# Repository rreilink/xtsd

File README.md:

XTSD 
====

XTSD is an ISA card that adds an SD-card slot to old PCs using an ISA interface. This project is work in progress.

Repo structure
--------------

| folder | description |
|--------|-------------|
|hardware| Schematic and PCB design in KiCAD |
|hardware-output | Schematic as PDF and Gerber layout files for ordering the PCB |
|GAL | Source and JEDEC binary file for the programmable logic chip U6 (ATF22V10) |

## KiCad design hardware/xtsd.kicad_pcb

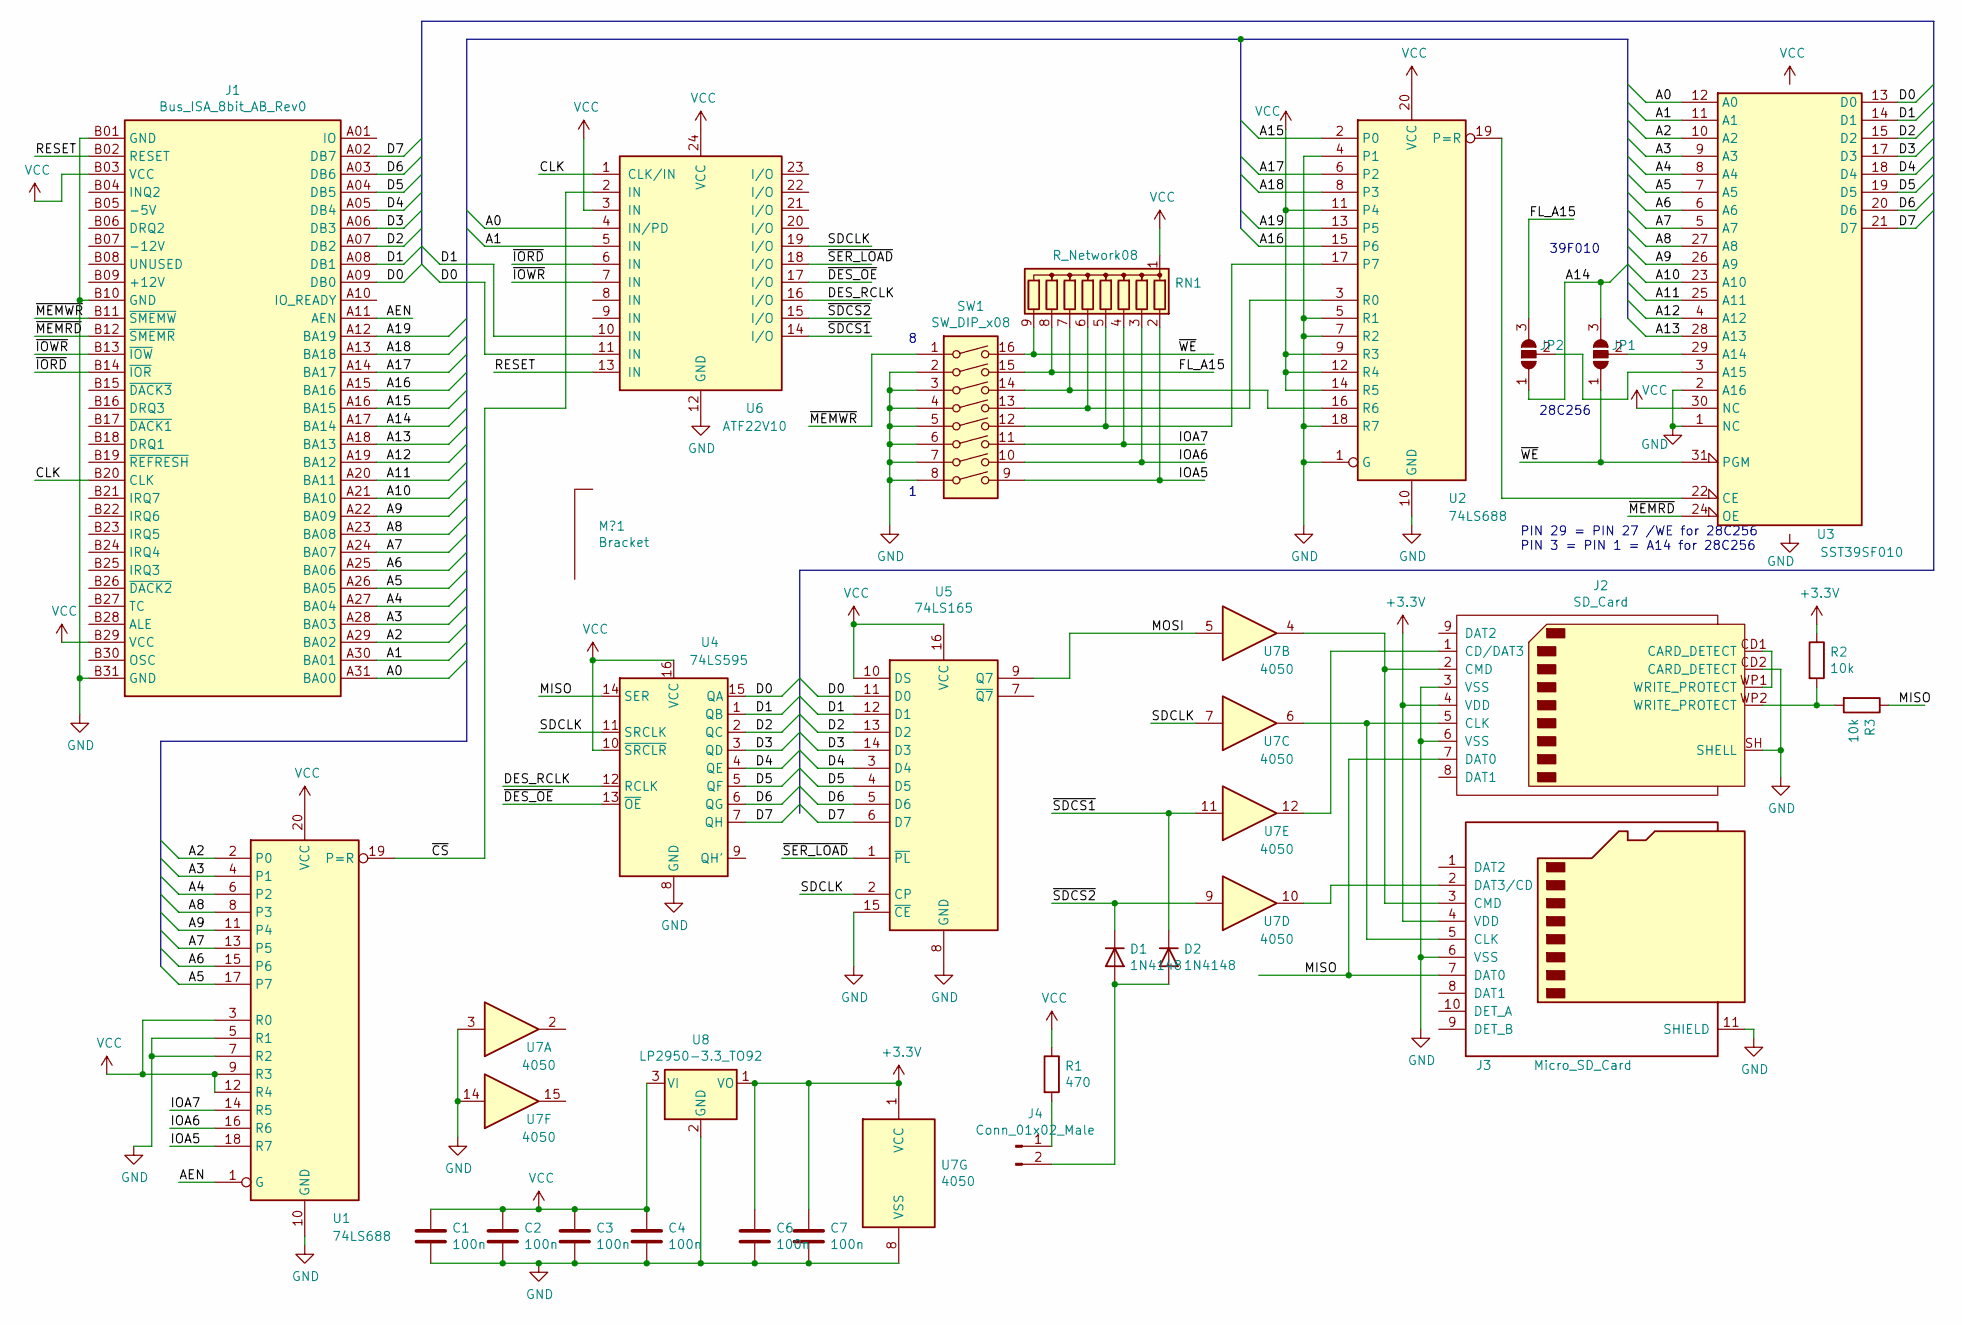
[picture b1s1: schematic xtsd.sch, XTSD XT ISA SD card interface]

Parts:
C1, C2, C3, C4, C6, C7: 100n; C_Disc_D4.3mm_W1.9mm_P5.00mm
D1, D2: 1N4148; D_DO-35_SOD27_P7.62mm_Horizontal
J1: Bus_ISA_8bit_AB_Rev0; ISA_CARD_EDGE_CONNECTOR_8BIT_Rev1
J2: SD_Card; Molex_503500-0991
J3: Micro_SD_Card; microSD_HC_Molex_104031-0811; Farnell 2678573
J4: Conn_01x02_Male; PinHeader_1x02_P2.54mm_Horizontal
JP1, JP2: SolderJumper_3_Open; SolderJumper-3_P2.0mm_Open_TrianglePad1.0x1.5mm_NumberLabels
M?1: Bracket; PC_BRACKET_ISA_KEYSTONE_9202_Rev1
R1: 470; R_Axial_DIN0207_L6.3mm_D2.5mm_P7.62mm_Horizontal
R2, R3: 10k; R_Axial_DIN0207_L6.3mm_D2.5mm_P7.62mm_Horizontal
RN1: R_Network08; R_Array_SIP9
SW1: SW_DIP_x08; SW_DIP_SPSTx08_Slide_9.78x22.5mm_W7.62mm_P2.54mm
U1, U2: 74LS688; DIP-20_W7.62mm_LongPads
U3: SST39SF010; DIP-32_W15.24mm_Socket_LongPads
U4: 74LS595; DIP-16_W7.62mm_LongPads
U5: 74LS165; DIP-16_W7.62mm_LongPads
U6: ATF22V10; DIP-24_W7.62mm_Socket_LongPads
U7: 4050; DIP-16_W7.62mm_LongPads
U8: LP2950-3.3_TO92; TO-92_Inline

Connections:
+3V3: C6.1, C7.1, J2.4 (VDD), J3.4 (VDD), R2.1, U7.1 (VCC), U8.1 (VO)
/A0: J1.A31 (BA00), U3.12 (A0), U6.4 (IN/PD)
/A1: J1.A30 (BA01), U3.11 (A1), U6.5 (IN)
/A2: J1.A29 (BA02), U1.2 (P0), U3.10 (A2)
/A3: J1.A28 (BA03), U1.4 (P1), U3.9 (A3)
/A4: J1.A27 (BA04), U1.6 (P2), U3.8 (A4)
/A5: J1.A26 (BA05), U1.17 (P7), U3.7 (A5)
/A6: J1.A25 (BA06), U1.15 (P6), U3.6 (A6)
/A7: J1.A24 (BA07), U1.13 (P5), U3.5 (A7)
/A8: J1.A23 (BA08), U1.8 (P3), U3.27 (A8)
/A9: J1.A22 (BA09), U1.11 (P4), U3.26 (A9)
/A10: J1.A21 (BA10), U3.23 (A10)
/A11: J1.A20 (BA11), U3.25 (A11)
/A12: J1.A19 (BA12), U3.4 (A12)
/A13: J1.A18 (BA13), U3.28 (A13)
/A14: J1.A17 (BA14), JP1.3 (B), JP2.1 (A)
/A15: J1.A16 (BA15), U2.2 (P0)
/A16: J1.A15 (BA16), U2.15 (P6)
/A17: J1.A14 (BA17), U2.6 (P2)
/A18: J1.A13 (BA18), U2.8 (P3)
/A19: J1.A12 (BA19), U2.13 (P5)
/AEN: J1.A11 (AEN), U1.1 (G)
/CLK: J1.B20 (CLK), U6.1 (CLK/IN)
/D0: J1.A09 (DB0), U3.13 (D0), U4.15 (QA), U5.11 (D0), U6.11 (IN)
/D1: J1.A08 (DB1), U3.14 (D1), U4.1 (QB), U5.12 (D1), U6.10 (IN)
/D2: J1.A07 (DB2), U3.15 (D2), U4.2 (QC), U5.13 (D2)
/D3: J1.A06 (DB3), U3.17 (D3), U4.3 (QD), U5.14 (D3)
/D4: J1.A05 (DB4), U3.18 (D4), U4.4 (QE), U5.3 (D4)
/D5: J1.A04 (DB5), U3.19 (D5), U4.5 (QF), U5.4 (D5)
/D6: J1.A03 (DB6), U3.20 (D6), U4.6 (QG), U5.5 (D6)
/D7: J1.A02 (DB7), U3.21 (D7), U4.7 (QH), U5.6 (D7)
/DES_RCLK: U4.12 (RCLK), U6.16 (I/O)
/FL_A15: JP2.3 (B), RN1.8 (R7), SW1.15
/IOA5: RN1.2 (R1), SW1.9, U1.18 (R7)
/IOA6: RN1.3 (R2), SW1.10, U1.16 (R6)
/IOA7: RN1.4 (R3), SW1.11, U1.14 (R5)
/MISO: J2.7 (DAT0), J3.7 (DAT0), R3.1, U4.14 (SER)
/MOSI: U5.9 (Q7), U7.5
/RESET: J1.B02 (RESET), U6.13 (IN)
/SDCLK: U4.11 (SRCLK), U5.2 (CP), U6.19 (I/O), U7.7
/~CS~: U1.19 (P=R), U6.2 (IN)
/~DES_OE~: U4.13 (~OE), U6.17 (I/O)
/~IORD~: J1.B14 (~IOR), U6.6 (IN)
/~IOWR~: J1.B13 (~IOW), U6.7 (IN)
/~MEMRD~: J1.B12 (~SMEMR), U3.24 (OE)
/~MEMWR~: J1.B11 (~SMEMW), SW1.1
/~SDCS1~: D2.1 (K), U6.14 (I/O), U7.11
/~SDCS2~: D1.1 (K), U6.15 (I/O), U7.9
/~SER_LOAD~: U5.1 (~PL), U6.18 (I/O)
/~WE~: JP1.1 (A), RN1.9 (R8), SW1.16, U3.31 (PGM)
GND: C1.2, C2.2, C3.2, C4.2, C6.2, C7.2, J1.B01 (GND), J1.B10 (GND), J1.B31 (GND), J2.3 (VSS), J2.6 (VSS), J2.CD2 (CARD_DETECT), J2.SH (SHELL), J3.6 (VSS), J3.11 (SHIELD), SW1.2, SW1.3, SW1.4, SW1.5, SW1.6, SW1.7, SW1.8, U1.5 (R1), U1.7 (R2), U1.10 (GND), U2.1 (G), U2.4 (P1), U2.5 (R1), U2.7 (R2), U2.10 (GND), U2.18 (R7), U3.1 (NC), U3.2 (A16), U3.16 (GND), U4.8 (GND), U5.8 (GND), U5.15 (~CE), U6.12 (GND), U7.3, U7.8 (VSS), U7.14, U8.2 (GND)
unnamed: D1.2 (A), D2.2 (A), J4.2
unnamed: J2.1 (CD/DAT3), U7.12
unnamed: J2.2 (CMD), J3.3 (CMD), U7.4
unnamed: J2.5 (CLK), J3.5 (CLK), U7.6
unnamed: J2.CD1 (CARD_DETECT), J2.WP1 (WRITE_PROTECT)
unnamed: J2.WP2 (WRITE_PROTECT), R2.2, R3.2
unnamed: J3.2 (DAT3/CD), U7.10
unnamed: J4.1, R1.2
unnamed: JP1.2 (C), U3.29 (A14)
unnamed: JP2.2 (C), U3.3 (A15)
unnamed: RN1.5 (R4), SW1.12, U2.17 (P7)
unnamed: RN1.6 (R5), SW1.13, U2.3 (R0)
unnamed: RN1.7 (R6), SW1.14, U2.16 (R6)
unnamed: U2.19 (P=R), U3.22 (CE)
VCC: C1.1, C2.1, C3.1, C4.1, J1.B03 (VCC), J1.B29 (VCC), R1.1, RN1.1 (common), U1.3 (R0), U1.9 (R3), U1.12 (R4), U1.20 (VCC), U2.9 (R3), U2.11 (P4), U2.12 (R4), U2.14 (R5), U2.20 (VCC), U3.30 (NC), U3.32 (VCC), U4.10 (~SRCLR), U4.16 (VCC), U5.10 (DS), U5.16 (VCC), U6.3 (IN), U6.24 (VCC), U8.3 (VI)

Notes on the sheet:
PIN 29 = PIN 27 /WE for 28C256 PIN 3 = PIN 1 = A14 for 28C256
28C256
39F010

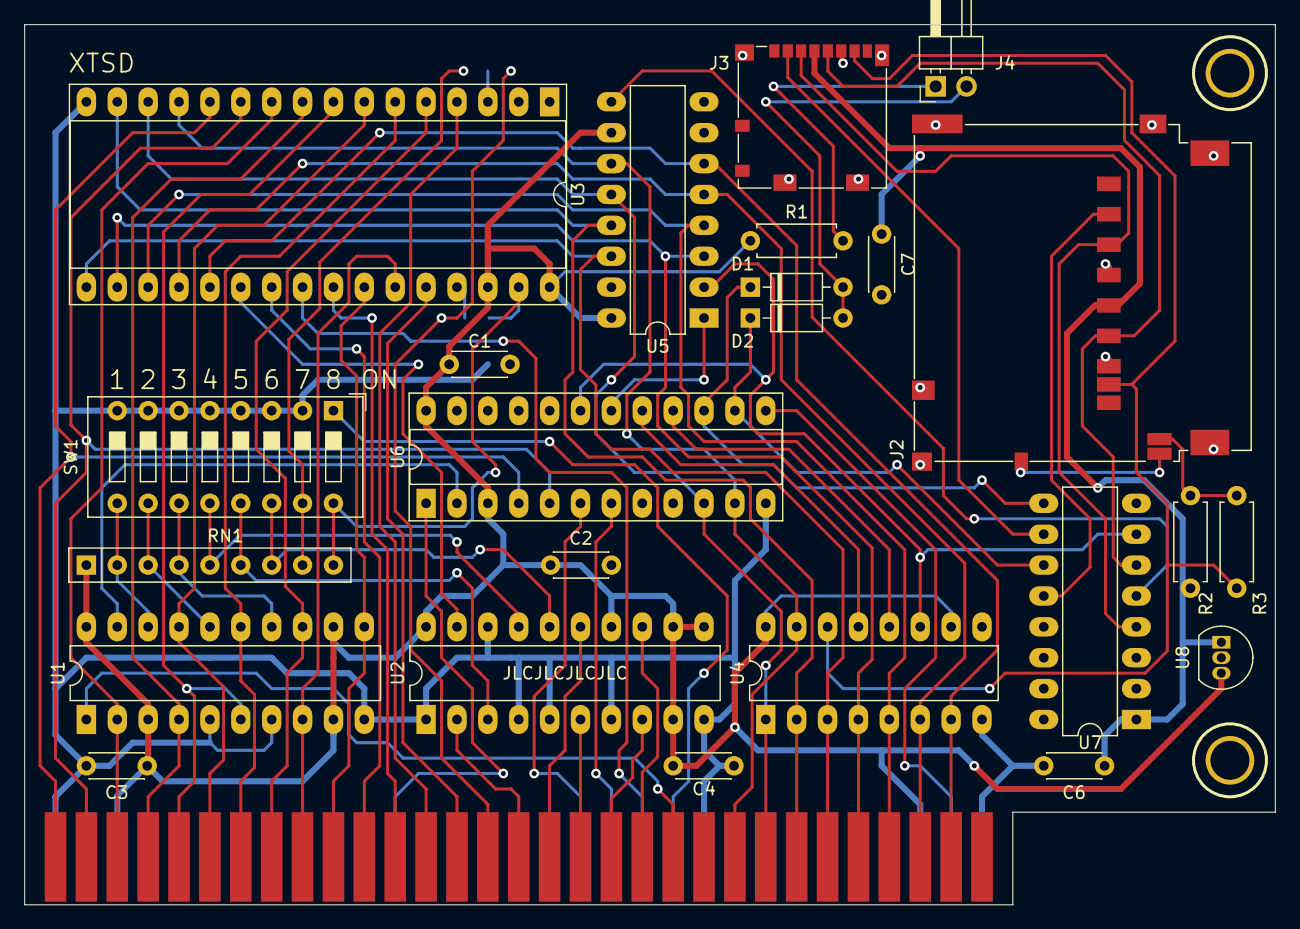
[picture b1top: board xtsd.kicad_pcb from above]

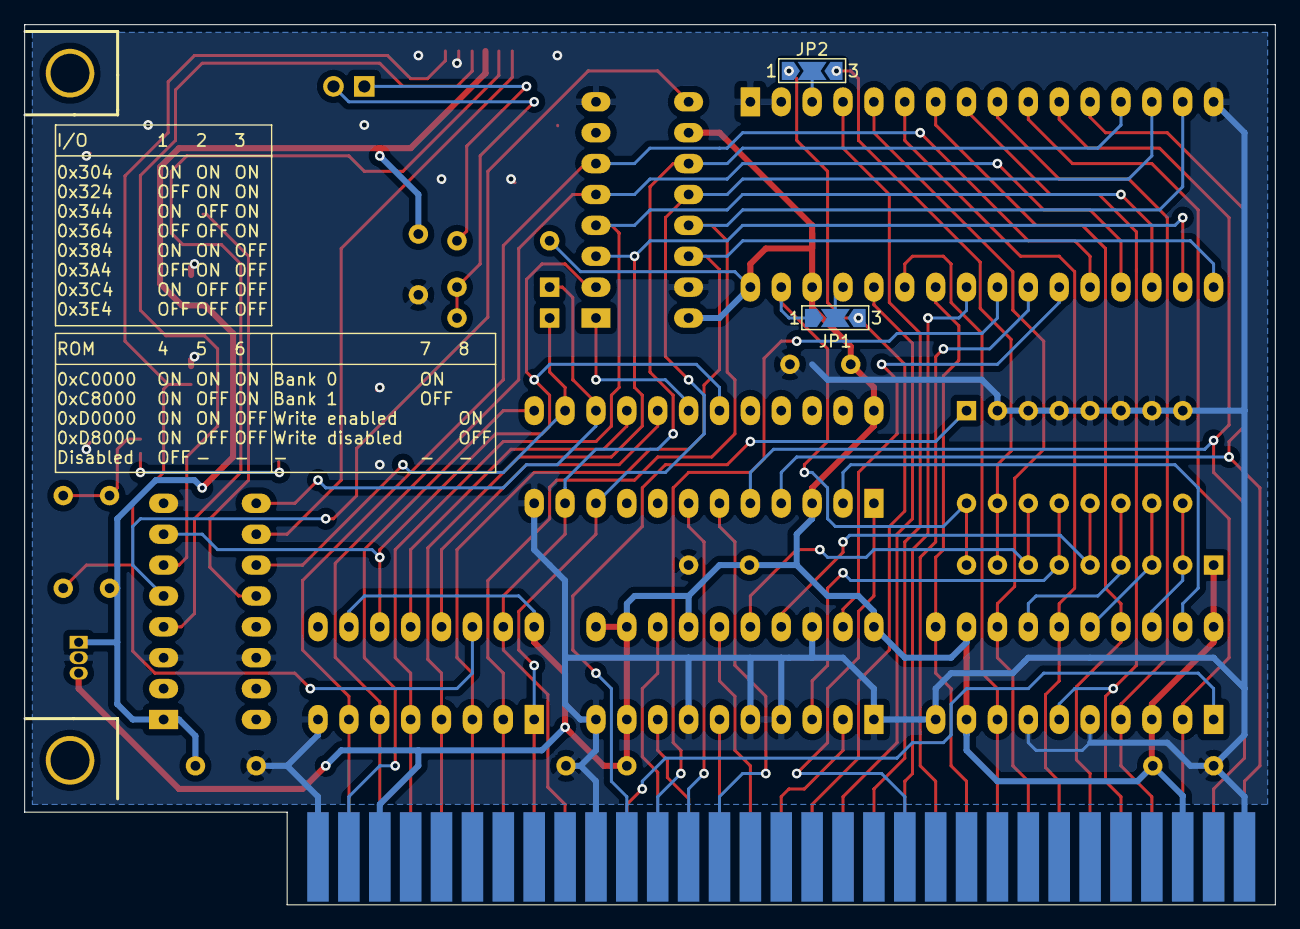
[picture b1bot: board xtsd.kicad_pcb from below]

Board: 2 copper layers, 102.9 x 72.4 mm, 28 parts (2 on the bottom side), 66 nets.

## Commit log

2022-05-15 Initial import
2022-05-15 As ordered
2022-07-23 fix: U4 /SRCLR should be connected to VCC instead of GND
2024-08-19 Added GAL source and JEDEC file; added schematic as PDF
2024-08-19 Added README.md
